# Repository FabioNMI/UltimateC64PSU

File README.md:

Welcome to the Ultimate Commodore 64 Power Supply!

This circuit is designed to power a Commodore 64 computer without the use of bulky transformers and by generating pseudo-AC (9Vrms) and 5Vdc to power the machine.

Please use it at your own risk, there are no guarantees that this circuit is safe as it is not certified in any way!

Link to the video in the NMI channel: https://youtu.be/_GyQUuKDc-I

There are two version that differ only in the PCB form-factor:

v7_front is the format featured in my video (power output in the front)

v8_back is a different layout with all connections on the back

Enjoy!

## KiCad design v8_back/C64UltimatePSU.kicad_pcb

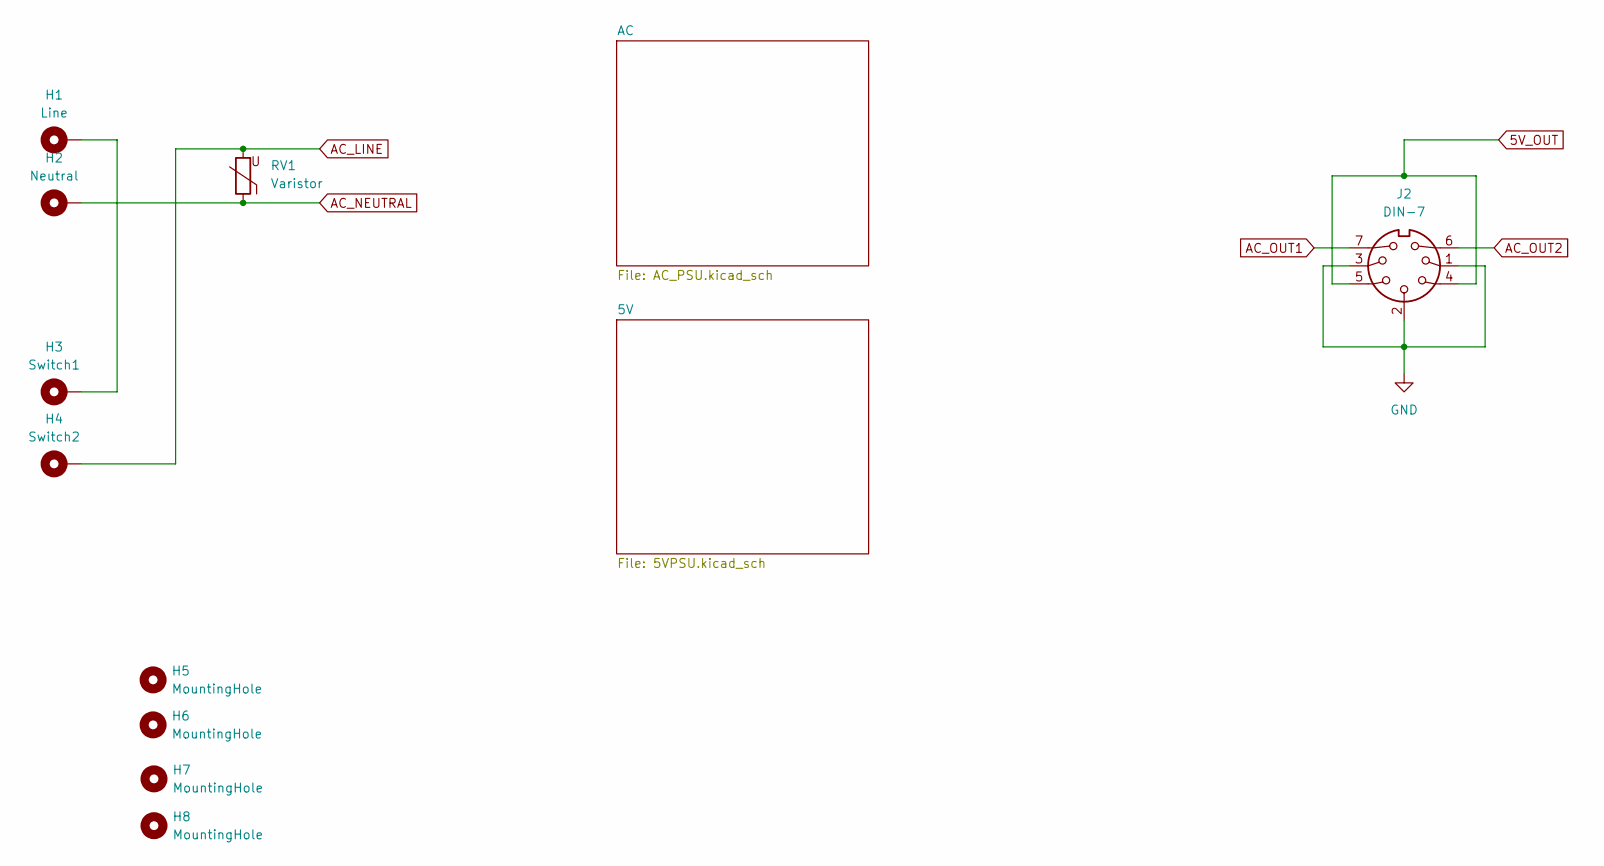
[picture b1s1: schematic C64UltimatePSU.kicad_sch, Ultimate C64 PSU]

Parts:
H1: Line; MountingHole_2.5mm_Pad
H2: Neutral; MountingHole_2.5mm_Pad
H3: Switch1; MountingHole_2.5mm_Pad
H4: Switch2; MountingHole_2.5mm_Pad
H5, H6, H7, H8: MountingHole; MountingHole_3.5mm
J2: DIN-7; POWER_CON_DIN7
RV1: Varistor; RV_Disc_D7mm_W4mm_P5mm

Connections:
5V_OUT: J2.4, J2.5; also elsewhere on the board
AC_LINE: H4.1, RV1.2; also elsewhere on the board
AC_NEUTRAL: H2.1, RV1.1; also elsewhere on the board
AC_OUT1: J2.7; also elsewhere on the board
AC_OUT2: J2.6; also elsewhere on the board
GND: J2.1, J2.2, J2.3; also elsewhere on the board
unnamed: H1.1, H3.1

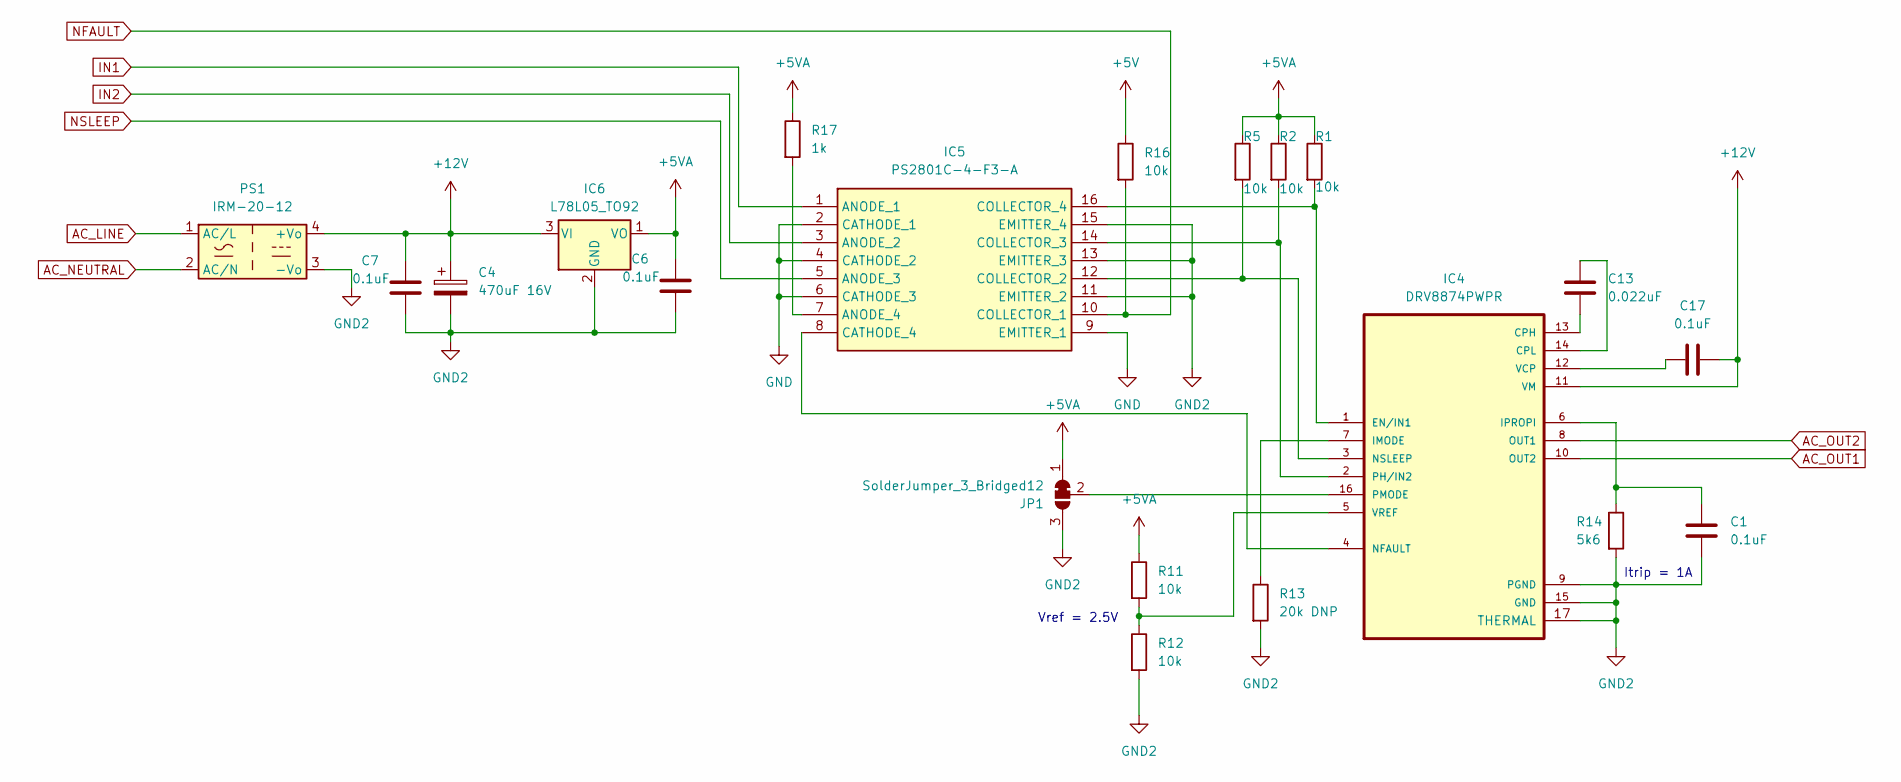
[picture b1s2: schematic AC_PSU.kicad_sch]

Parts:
C1, C6, C7, C17: 0.1uF; C_0805_2012Metric_Pad1.18x1.45mm_HandSolder
C4: 470uF 16V; CP_Radial_D6.3mm_P2.50mm
C13: 0.022uF; C_0805_2012Metric_Pad1.18x1.45mm_HandSolder
IC4: DRV8874PWPR; SOP65P640X120-17N
IC5: PS2801C-4-F3-A; SOIC-16_4.55x10.3mm_P1.27mm; Manufacturer_Part_Number PS2801C-4-F3-A
IC6: L78L05_TO92; TO-92_Inline
JP1: SolderJumper_3_Bridged12; SolderJumper-3_P1.3mm_Bridged12_Pad1.0x1.5mm_NumberLabels
PS1: IRM-20-12; Converter_ACDC_MeanWell_IRM-20-xx_THT
R1, R2, R5, R11, R12, R16: 10k; R_0805_2012Metric_Pad1.20x1.40mm_HandSolder
R13: 20k DNP; R_0805_2012Metric_Pad1.20x1.40mm_HandSolder
R14: 5k6; R_0805_2012Metric_Pad1.20x1.40mm_HandSolder
R17: 1k; R_0805_2012Metric_Pad1.20x1.40mm_HandSolder

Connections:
+5V: R16.1; also elsewhere on the board
+5VA: C6.2, IC6.1 (VO), JP1.1 (A), R1.1, R2.1, R5.1, R11.1, R17.1
+12V: C4.1, C7.2, C17.2, IC4.11 (VM), IC6.3 (VI), PS1.4 (+Vo)
AC_LINE: PS1.1 (AC/L); also elsewhere on the board
AC_NEUTRAL: PS1.2 (AC/N); also elsewhere on the board
AC_OUT1: IC4.10 (OUT2); also elsewhere on the board
AC_OUT2: IC4.8 (OUT1); also elsewhere on the board
GND: IC5.2 (CATHODE_1), IC5.4 (CATHODE_2), IC5.6 (CATHODE_3), IC5.9 (EMITTER_1); also elsewhere on the board
GND2: C1.2, C4.2, C6.1, C7.1, IC4.9 (PGND), IC4.15 (GND), IC4.17 (THERMAL), IC5.11 (EMITTER_2), IC5.13 (EMITTER_3), IC5.15 (EMITTER_4), IC6.2 (GND), JP1.3 (B), PS1.3 (-Vo), R12.2, R13.2, R14.2
IN1: IC5.1 (ANODE_1); also elsewhere on the board
IN2: IC5.3 (ANODE_2); also elsewhere on the board
NFAULT: IC5.10 (COLLECTOR_1), R16.2; also elsewhere on the board
NSLEEP: IC5.5 (ANODE_3); also elsewhere on the board
unnamed: C13.2, IC4.13 (CPH)
unnamed: C13.1, IC4.14 (CPL)
unnamed: IC4.1 (EN/IN1), IC5.16 (COLLECTOR_4), R1.2
unnamed: IC4.7 (IMODE), R13.1
unnamed: C1.1, IC4.6 (IPROPI), R14.1
unnamed: IC4.4 (NFAULT), IC5.8 (CATHODE_4)
unnamed: IC4.3 (NSLEEP), IC5.12 (COLLECTOR_2), R5.2
unnamed: IC4.2 (PH/IN2), IC5.14 (COLLECTOR_3), R2.2
unnamed: IC4.16 (PMODE), JP1.2 (C)
unnamed: C17.1, IC4.12 (VCP)
unnamed: IC4.5 (VREF), R11.2, R12.1
unnamed: IC5.7 (ANODE_4), R17.2

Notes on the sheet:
Vref = 2.5V
Itrip = 1A

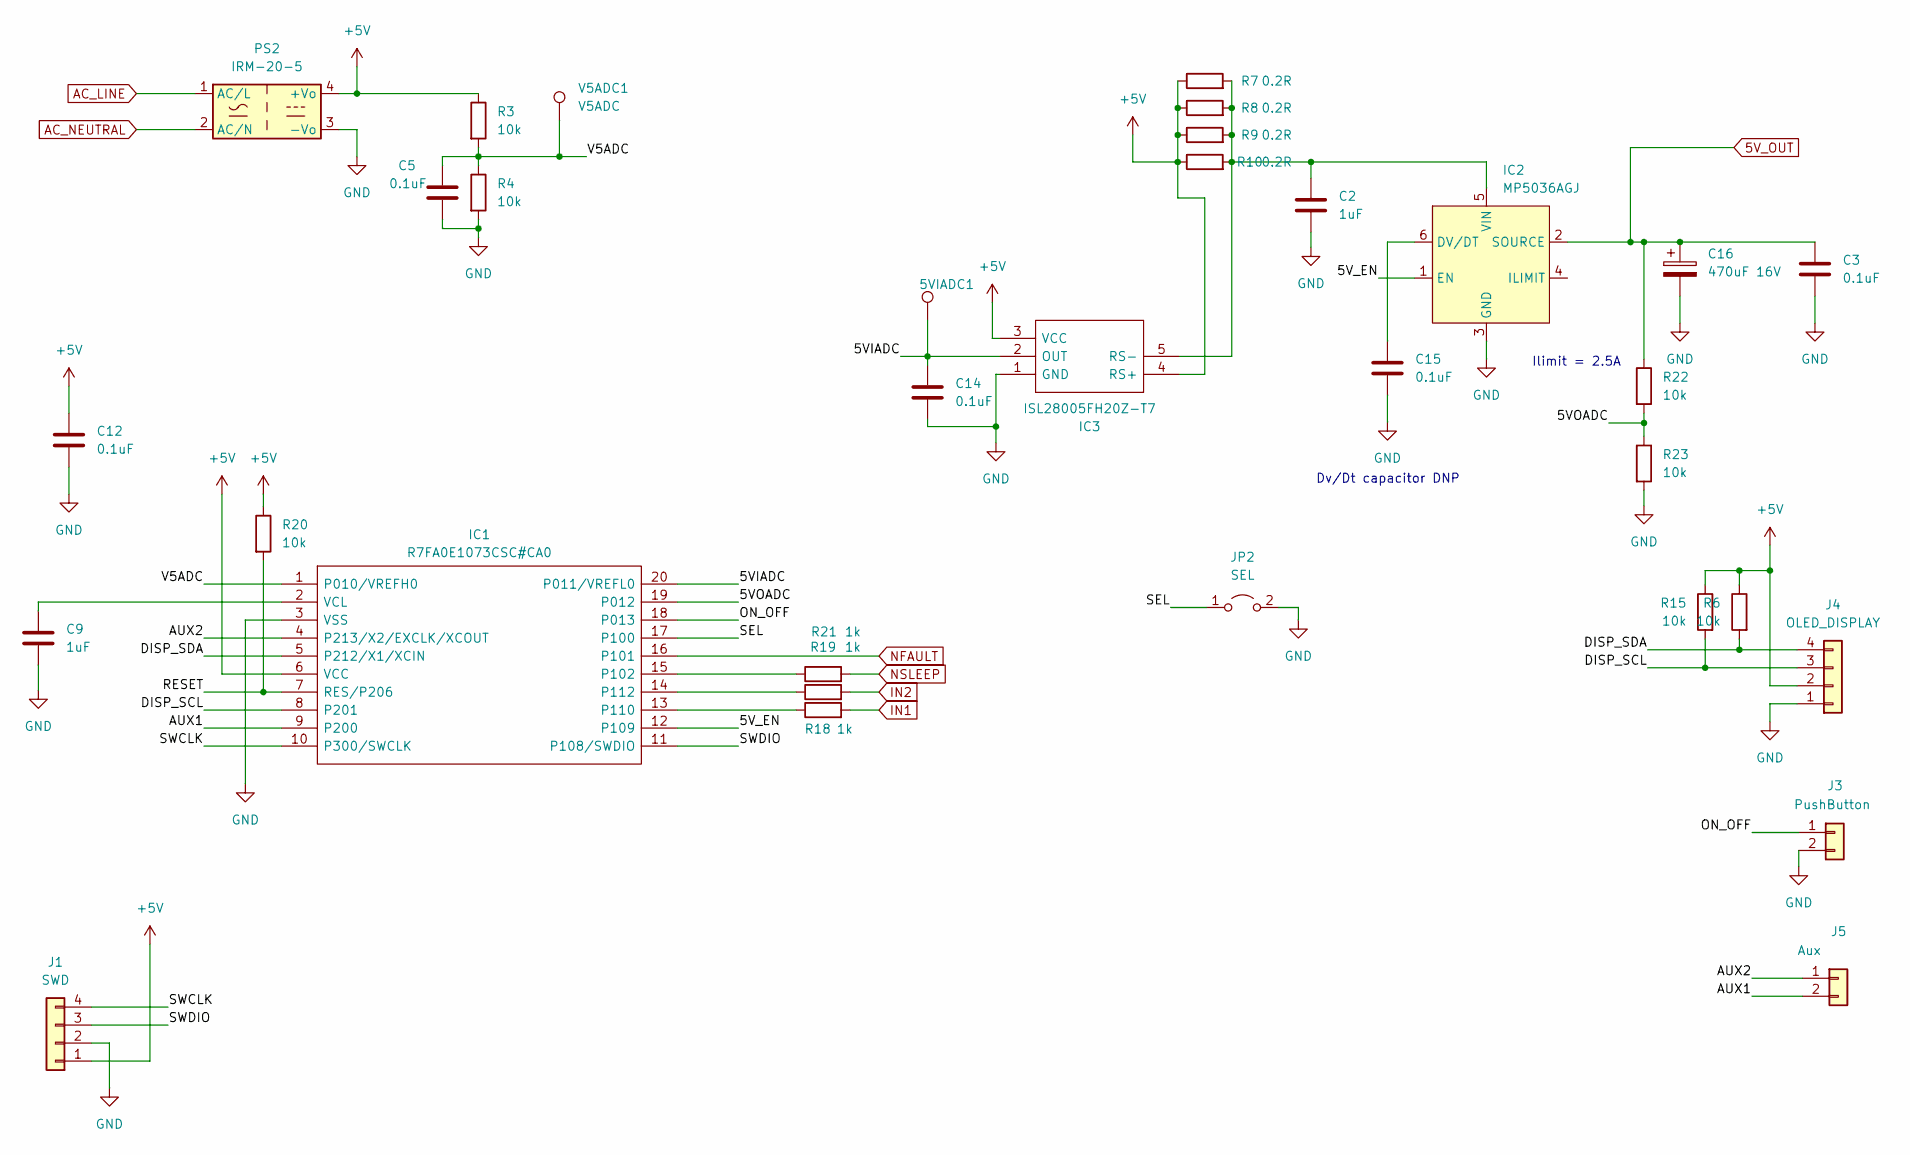
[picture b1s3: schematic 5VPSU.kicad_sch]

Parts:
5VIADC1: TestPoint_Pad_D1.0mm
C2, C9: 1uF; C_0805_2012Metric_Pad1.18x1.45mm_HandSolder
C3, C5, C12, C14, C15: 0.1uF; C_0805_2012Metric_Pad1.18x1.45mm_HandSolder
C16: 470uF 16V; CP_Radial_D6.3mm_P2.50mm
IC1: R7FA0E1073CSC#CA0; SSOP-20_4.4x6.5mm_P0.65mm; Manufacturer_Part_Number R7FA0E1073CSC#CA0
IC2: MP5036AGJ; SOT-23-6_Handsoldering
IC3: ISL28005FH20Z-T7; SOT-23-5_HandSoldering; Manufacturer_Part_Number ISL28005FH20Z-T7; Mouser Part Number 968-ISL28005FH20Z-T7
J1: SWD; PinHeader_1x04_P2.54mm_Vertical
J3: PushButton; PinHeader_1x02_P2.54mm_Vertical
J4: OLED_DISPLAY; PinHeader_1x04_P2.54mm_Vertical
J5: Aux; PinHeader_1x02_P2.54mm_Vertical
JP2: SEL; PinHeader_1x02_P2.54mm_Vertical
PS2: IRM-20-5; Converter_ACDC_MeanWell_IRM-20-xx_THT
R3, R4, R6, R15, R20, R22, R23: 10k; R_0805_2012Metric_Pad1.20x1.40mm_HandSolder
R7, R8, R9, R10: 0.2R; R_1206_3216Metric_Pad1.30x1.75mm_HandSolder
R18, R19, R21: 1k; R_0805_2012Metric_Pad1.20x1.40mm_HandSolder
V5ADC1: V5ADC; TestPoint_Pad_D1.0mm

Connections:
5V_OUT: C3.2, C16.1, IC2.2 (SOURCE), R22.1; also elsewhere on the board
+5V: C12.2, IC1.6 (VCC), IC3.3 (VCC), IC3.4 (RS+), J1.1, J4.2, PS2.4 (+Vo), R3.1, R6.1, R7.1, R8.1, R9.1, R10.1, R15.1, R20.1; also elsewhere on the board
/5V/5VIADC: 5VIADC1.1, C14.2, IC1.20 (P011/VREFL0), IC3.2 (OUT)
/5V/5VOADC: IC1.19 (P012), R22.2, R23.1
/5V/5V_EN: IC1.12 (P109), IC2.1 (EN)
/5V/AUX1: IC1.9 (P200), J5.2
/5V/AUX2: IC1.4 (P213/X2/EXCLK/XCOUT), J5.1
/5V/DISP_SCL: IC1.8 (P201), J4.3, R15.2
/5V/DISP_SDA: IC1.5 (P212/X1/XCIN), J4.4, R6.2
/5V/ON_OFF: IC1.18 (P013), J3.1
/5V/RESET: IC1.7 (RES/P206), R20.2
/5V/SEL: IC1.17 (P100), JP2.1 (A)
/5V/SWCLK: IC1.10 (P300/SWCLK), J1.4
/5V/SWDIO: IC1.11 (P108/SWDIO), J1.3
/5V/V5ADC: C5.2, IC1.1 (P010/VREFH0), R3.2, R4.1, V5ADC1.1
AC_LINE: PS2.1 (AC/L); also elsewhere on the board
AC_NEUTRAL: PS2.2 (AC/N); also elsewhere on the board
GND: C2.1, C3.1, C5.1, C9.1, C12.1, C14.1, C15.1, C16.2, IC1.3 (VSS), IC2.3 (GND), IC3.1 (GND), J1.2, J3.2, J4.1, JP2.2 (B), PS2.3 (-Vo), R4.2, R23.2; also elsewhere on the board
IN1: R18.2; also elsewhere on the board
IN2: R19.2; also elsewhere on the board
NFAULT: IC1.16 (P101); also elsewhere on the board
NSLEEP: R21.2; also elsewhere on the board
unnamed: IC1.15 (P102), R21.1
unnamed: IC1.13 (P110), R18.1
unnamed: IC1.14 (P112), R19.1
unnamed: C9.2, IC1.2 (VCL)
unnamed: C15.2, IC2.6 (DV/DT)
unnamed: C2.2, IC2.5 (VIN), IC3.5 (RS-), R7.2, R8.2, R9.2, R10.2

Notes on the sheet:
Dv/Dt capacitor DNP
Ilimit = 2.5A

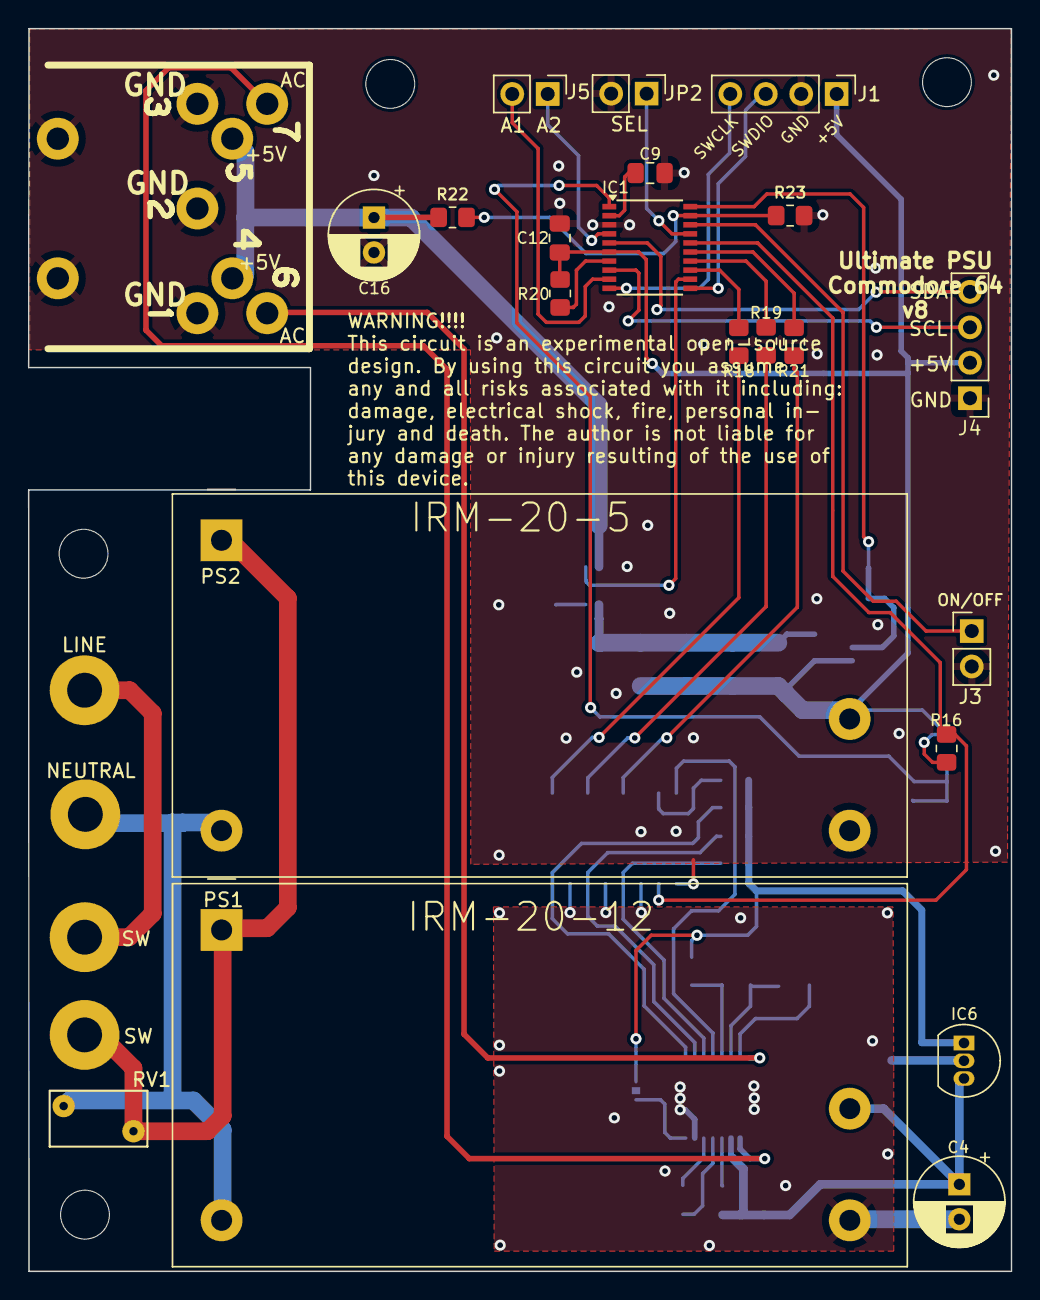
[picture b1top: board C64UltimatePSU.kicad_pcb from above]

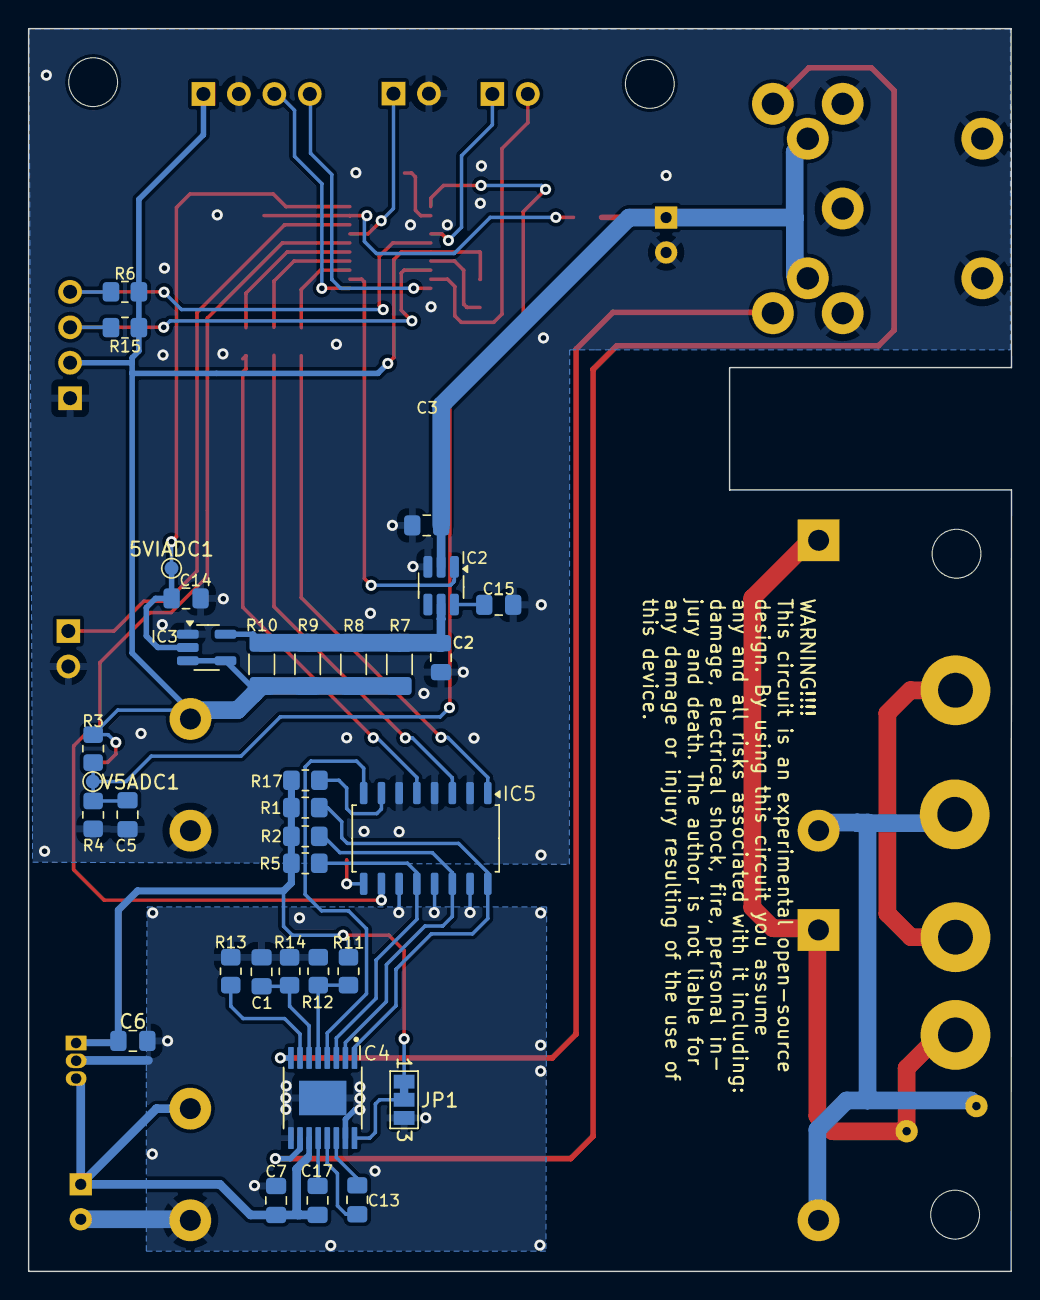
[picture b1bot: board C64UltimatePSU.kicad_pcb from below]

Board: 2 copper layers, 70.4 x 89.0 mm, 63 parts (33 on the bottom side), 46 nets.

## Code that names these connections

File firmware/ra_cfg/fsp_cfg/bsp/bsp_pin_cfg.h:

/* generated configuration header file - do not edit */
#ifndef BSP_PIN_CFG_H_
#define BSP_PIN_CFG_H_
#include "r_ioport.h"

/* Common macro for FSP header files. There is also a corresponding FSP_FOOTER macro at the end of this file. */
FSP_HEADER

#define V_ADC (BSP_IO_PORT_00_PIN_10)
#define I_ADC (BSP_IO_PORT_00_PIN_11)
#define VO_ADC (BSP_IO_PORT_00_PIN_12)
#define ON_OFF (BSP_IO_PORT_00_PIN_13)
#define FREQ_SEL (BSP_IO_PORT_01_PIN_00)
#define PIN_AC_FAULT (BSP_IO_PORT_01_PIN_01)
#define PIN_AC_SLEEP (BSP_IO_PORT_01_PIN_02)
#define PIN_5V_EN (BSP_IO_PORT_01_PIN_09)
#define PIN_AC_IN1 (BSP_IO_PORT_01_PIN_10)
#define PIN_AC_IN2 (BSP_IO_PORT_01_PIN_12)
#define AUX1 (BSP_IO_PORT_02_PIN_00)
#define AUX2 (BSP_IO_PORT_02_PIN_13)
extern const ioport_cfg_t g_bsp_pin_cfg; /* R7FA0E1073CFJ.pincfg */

void BSP_PinConfigSecurityInit();

/* Common macro for FSP header files. There is also a corresponding FSP_HEADER macro at the top of this file. */
FSP_FOOTER
#endif /* BSP_PIN_CFG_H_ */

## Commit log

2025-03-07 Moved repository
2025-03-07 Moved to version folder
2025-03-07 Updated folder names, added v8
2025-03-07 Fixed readme
2025-06-02 Added firmware
